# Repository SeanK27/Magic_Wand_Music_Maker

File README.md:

# Magic Wand Music Maker

CU Boulder ECEN 1400 Project: Magic Wand Music Maker. Aimed towards making an accessible and interactive music making device.

## Installation

Use the package manager [pip](https://pip.pypa.io/en/stable/) to install required libraries.

```bash
pip install -r requirements.txt
```

## Setup
Enable serial port TTYS0 for UART communication on Raspberry Pi 3 and above.

Will add images of pinout in the future.

## Hardware
Uses WitMotion WT901 with Raspberry Pi 3. Custom PCB to interface between Raspberry Pi and WT901. Will include CAD files of full project in the future.

## Contributing

Pull requests are welcome. For major changes, please open an issue first
to discuss what you would like to change.

## License

[MIT](https://choosealicense.com/licenses/mit/)

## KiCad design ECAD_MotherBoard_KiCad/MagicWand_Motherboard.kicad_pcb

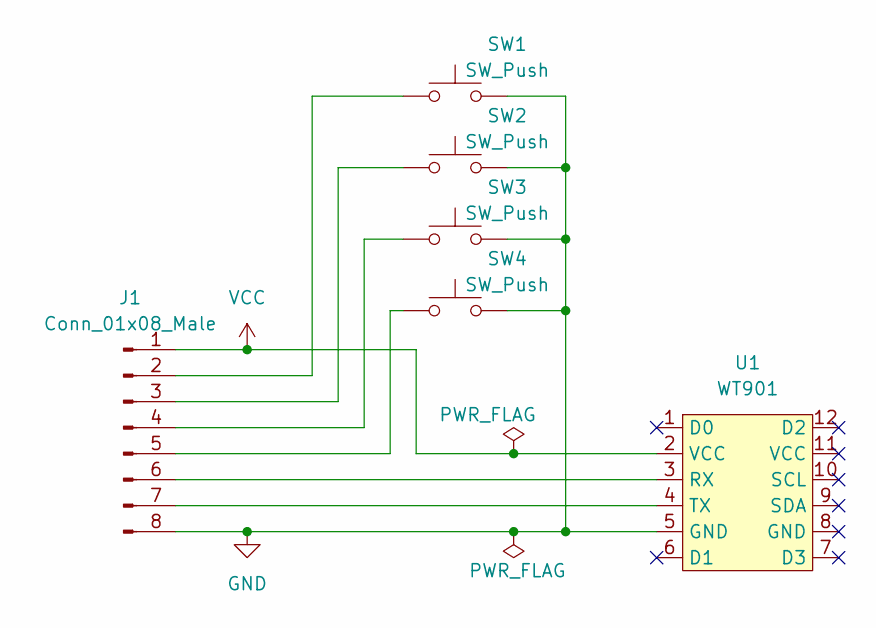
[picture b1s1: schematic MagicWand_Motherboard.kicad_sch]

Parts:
J1: Conn_01x08_Male; PinHeader_1x08_P2.54mm_Vertical
SW1, SW2, SW3, SW4: SW_Push; COM-10302
U1: WT901

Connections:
GND: J1.8, SW1.2, SW2.2, SW3.2, SW4.2, U1.5 (GND)
unnamed: J1.2, SW1.1
unnamed: J1.3, SW2.1
unnamed: J1.4, SW3.1
unnamed: J1.5, SW4.1
unnamed: J1.6, U1.3 (RX)
unnamed: J1.7, U1.4 (TX)
VCC: J1.1, U1.2 (VCC)

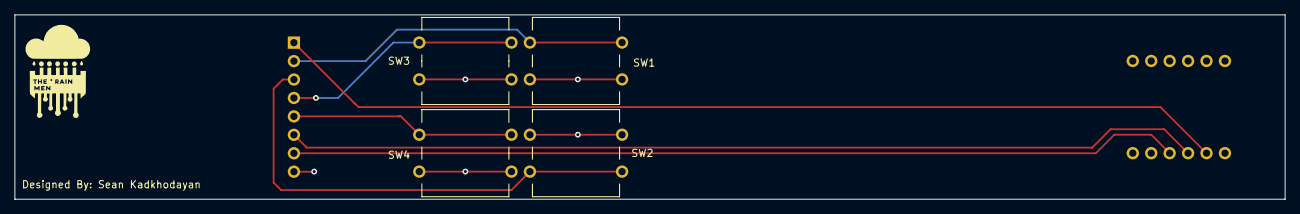
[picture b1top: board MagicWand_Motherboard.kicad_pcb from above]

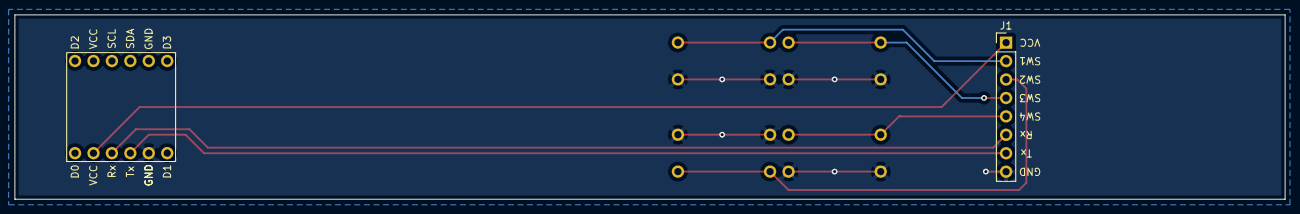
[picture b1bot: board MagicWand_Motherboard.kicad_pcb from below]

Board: 2 copper layers, 175.0 x 25.4 mm, 6 parts (2 on the bottom side), 8 nets.

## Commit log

2023-10-24 Create LICENSE
2023-10-24 Added README
2023-10-24 Added new file to copy into Raspberry Pi. Added functionality to increase and decrease volume of channel 1 through a button press
2023-10-26 Added multiple button support with pygame mixer.
2023-10-27 Organized File Directories
2023-10-28 Added multiple song compatibility. Made a button testing file.
2023-11-05 Add save to file Capitalized constants and added a save to file feature
2023-11-14 This code works! Added 4 button functionality and made some edits to work with new PCB.
2023-11-14 Added Electronics CAD files for Motherboard from KiCad.
2023-11-14 Added logo
2023-12-05 Created new script that includes the functionality of AbleNet button. Have not tested with Raspberry Pi, unsure if new song switch works.
2023-12-07 Bug fixes that prevents users from holding AbleNet button down. Fixed songList index error.
